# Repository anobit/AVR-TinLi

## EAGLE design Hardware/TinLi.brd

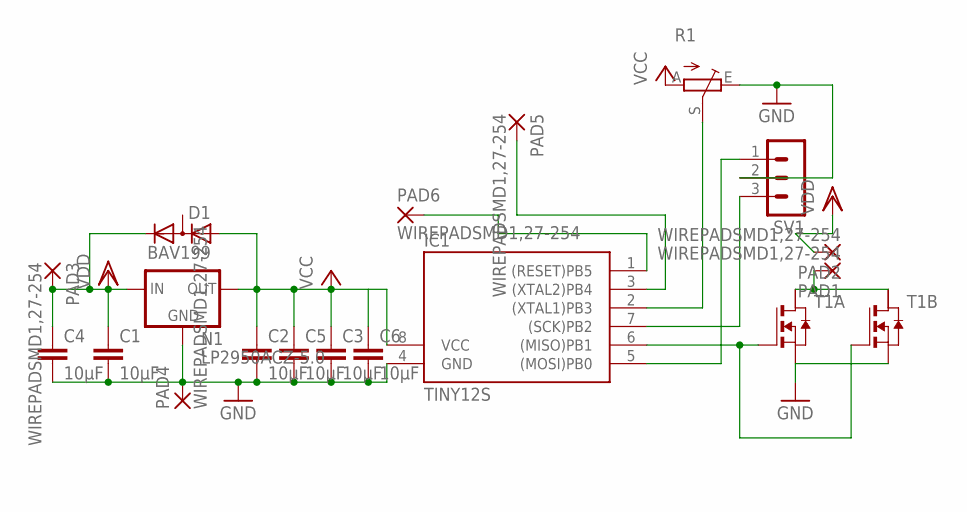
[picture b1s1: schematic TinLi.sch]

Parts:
C1, C2, C3, C4, C5, C6: 10µF; C1206
D1: BAV199; SOT23
IC1: TINY12S; SOIC8
N1: LP2950ACZ-5.0; TO92
PAD1, PAD2, PAD3, PAD4, PAD5, PAD6: WIREPADSMD1,27-254; SMD1,27-2,54
R1: TRIM_EU-CA6V; CA6V
SV1: MA03-1
T1: NMOS2SO8; SO8

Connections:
GND: C1.2, C2.2, C3.2, C4.2, C5.2, C6.2, IC1.4 (GND), N1.2 (GND), PAD4.1, R1.E, SV1.2, T1.1 (S), T1.3 (S)
unnamed: IC1.1 ((RESET)PB5), PAD6.1
unnamed: PAD1.1, T1.6 (D), T1.8 (D)
unnamed: IC1.3 ((XTAL2)PB4), PAD5.1
unnamed: IC1.6 ((MISO)PB1), T1.2 (G), T1.4 (G)
unnamed: IC1.7 ((SCK)PB2), SV1.3
unnamed: IC1.5 ((MOSI)PB0), SV1.1
unnamed: IC1.2 ((XTAL1)PB3), R1.S
VCC: C2.1, C3.1, C5.1, C6.1, D1.1 (A), IC1.8 (VCC), N1.1 (OUT), R1.A
VDD: C1.1, C4.1, D1.2 (C), N1.3 (IN), PAD2.1, PAD3.1

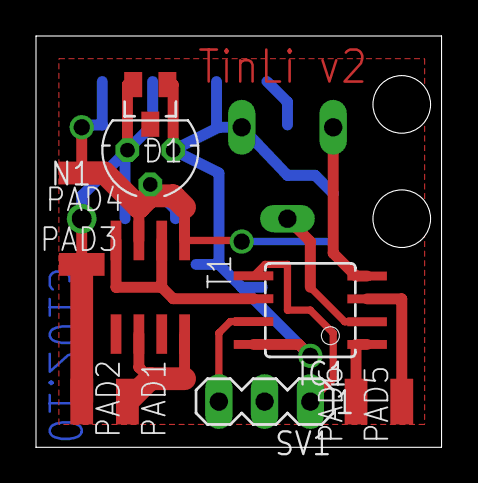
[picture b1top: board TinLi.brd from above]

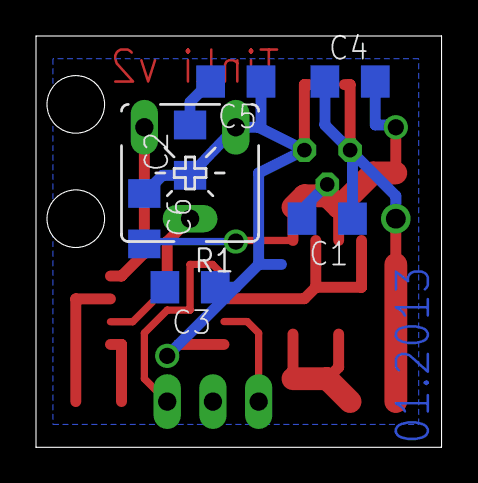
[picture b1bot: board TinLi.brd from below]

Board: 2 copper layers, 22.5 x 22.9 mm, 18 parts (7 on the bottom side), 10 nets.

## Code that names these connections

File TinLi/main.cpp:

/*
 * TinLi.cpp
 *
 * Created: 21.01.2017 13:35:13
 * Author : AnoBit
 */ 

#include <avr/io.h>

//Pinout
/*									_________
	  (PCINT5/(~RESET)/ADC0/dW)	PB5	|°		|	VCC
(PCINT3/XTAL1/CLKI/~(OC1B)/ADC3)PB3	|		|	PB2	(SCK/USCK/SCL/ADC1/T0/INT0/PCINT2)
(PCINT4/XTAL2/CLKO/OC1B/ADC2)	PB4 |		|	PB1	(MISO/DO/AIN1/OC0B/OC1A/PCINT1)
								GND |_______|	PB0	(MOSI/DI/SDA/AIN0/OC0A/~(OC1A)/AREF/PCINT0)
*/

//Böärd Cönnectiöns
/*

PIN		USAGE					DESCRIPTION

PB0		GPIO 1					Software UART / SPI / I2C?
PB1		PWM OUTPUT				PWM for Led Mosfet
PB2		GPIO 2					Software UART / SPI / I2C?
PB3		POTI INPUT				Set Maximum Current (Max Duty Cycle) / Set PWM Duty Cycle
PB4		GPIO 3 / ANALOG IN		GPIO / SPI / Set PWM Duty Cycle
PB5		GPIO 4 / (~RESET)		GPIO / SPI / Hardware Reset

*/

//NOTE: All inits are calculated for 1MHz operation.

#include "adc.h"
#include "pwm.h"
#include "scheduler.h"

void init(){
	
}

void cycle_10ms(){
	
}

void cycle_100ms(){
	
}

int main(void)
{
	init();
	
	while (1)
	{
		if(ISR_10MS){
			ISR_10MS = 0;
			cycle_10ms();
		}
		
		if(ISR_100MS){
			ISR_100MS = 0;
			cycle_100ms();
		}
	}
}

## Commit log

2017-01-21 Initial Setup
2017-01-21 Restructured Folder Added schematics
2017-01-21 Changed .gitignore
2017-01-21 Added Controller & Board Description
2017-01-21 added drivers
2017-01-30 Commit of working version
2017-01-30 Added main.c and project files
